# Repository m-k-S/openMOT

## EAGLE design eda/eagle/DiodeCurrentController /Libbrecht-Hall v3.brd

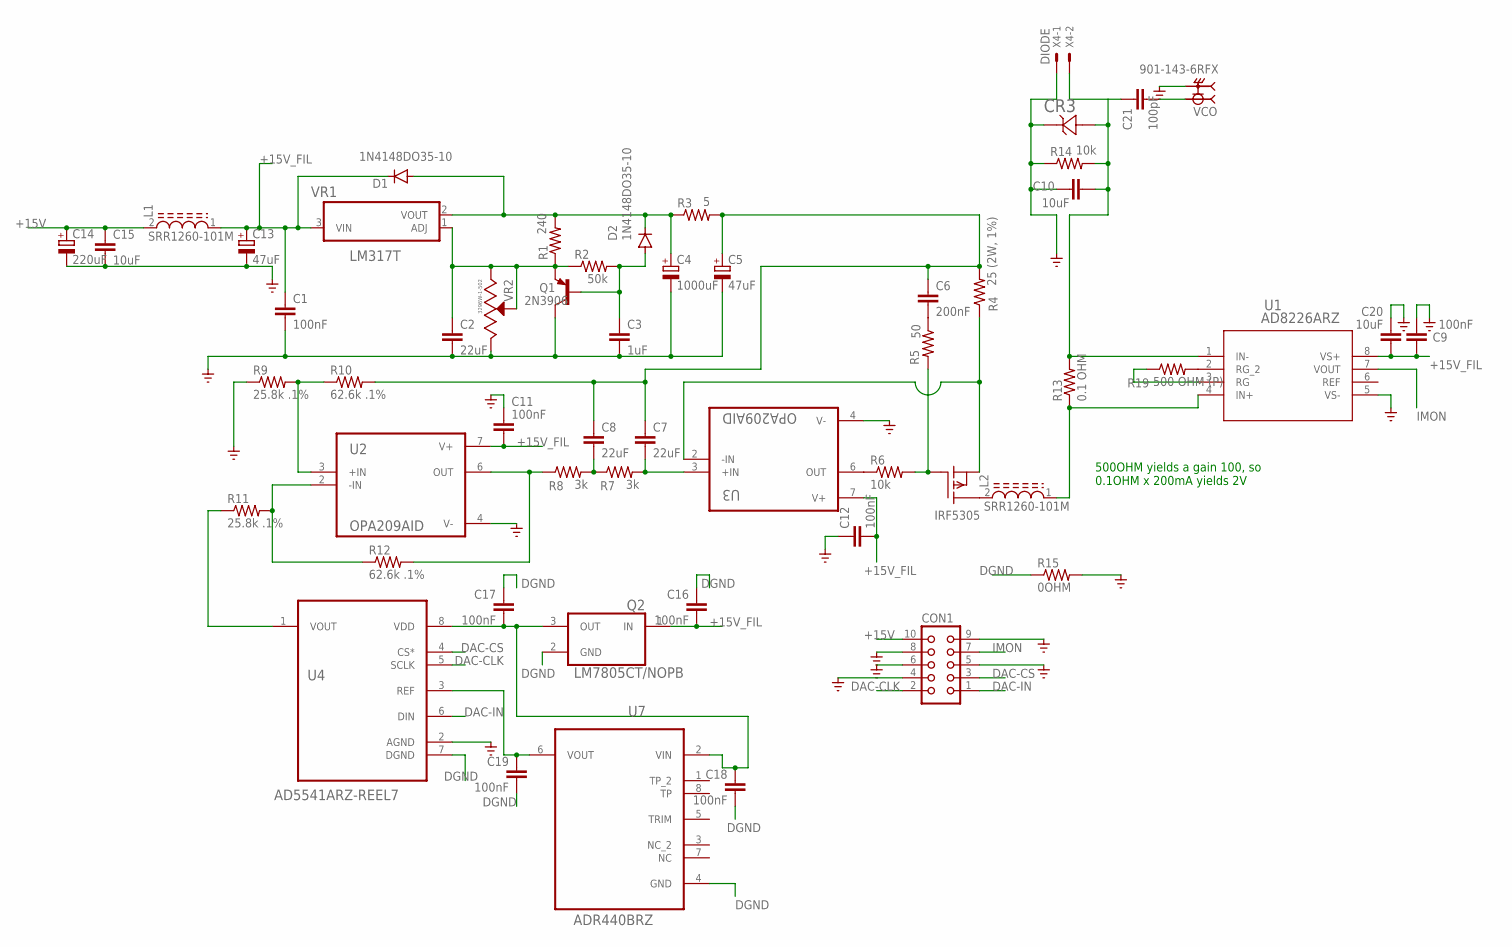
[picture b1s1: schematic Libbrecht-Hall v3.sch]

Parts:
C1, C11, C12, C16, C17, C18, C19: 100nF; C1206
C2, C7, C8: 22uF; C1206
C3: 1uF; C1206
C4: 1000uF; E5-13
C5, C13: 47uF; 175TMP-0808
C6: 200nF; C1206
C9: 100nF; C0603
C10, C15: 10uF; C1206
C14: 220uF; E3,5-8
C20: 10uF; C0603
C21: 100pF; C0603
CON1: CON10
CR3: ESDA7P60-1U1MZDO_1610_STM-M; ZDO_1610_STM-M
D1, D2: 1N4148DO35-10; DO35-10
IRF5305: IRF9530; TO220
L1, L2: SRR1260-101M; INDP125125X600N
Q1: 2N3906; TO92
Q2: LM7805CT/NOPB; TO254P1054X470X2600-3
R1: 240; R1206
R2: 50k; R1206
R3: 5; R1206
R4: 25 (2W, 1%); R1206
R5: 50; R1206
R6, R14: 10k; R1206
R7, R8: 3k; R1206
R9, R11: 25.8k .1%; R0603
R10, R12: 62.6k .1%; R0603
R13: 0.1 OHM; R1206
R15: 0OHM; R1206
R19: 500 OHM (P); R1206
U1: AD8226ARZ; R_8_ADI
U2, U3: OPA209AID; SOIC127P599X175-8N
U4: AD5541ARZ-REEL7; SOIC127P600X175-8N
U7: ADR440BRZ; SOIC127P600X175-8N
VCO: 901-143-6RFX; AMPHENOL_901-143-6RFX
VR1: LM317T; TO254P1054X470X1955-3
VR2: 3296W-1-502; TRIM_3296W-1-502
X4: DIODE; JST-XH-02-PACKAGE-LONG-PAD

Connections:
+15V: C14.+, C15.1, CON1.10, L1.2
+15V_FIL: C1.1, C9.2, C11.2, C12.2, C13.+, C16.2, C20.2, D1.C, L1.1, Q2.1 (IN), U1.8 (VS+), U2.7 (V+), U3.7 (V+), VR1.3 (VIN)
DAC-CLK: CON1.2, U4.5 (SCLK)
DAC-CS: CON1.3, U4.4 (CS*)
DAC-IN: CON1.1, U4.6 (DIN)
DGND: C16.1, C17.1, C18.2, C19.2, Q2.2 (GND), R15.1, U4.7 (DGND), U7.4 (GND)
GND: C1.2, C2.2, C3.2, C4.-, C5.-, C9.1, C10.1, C11.1, C12.1, C13.-, C14.-, C15.2, C20.1, CON1.4, CON1.5, CON1.6, CON1.8, CON1.9, CR3.1 (11), Q1.1 (C), R9.1, R14.1, R15.2, U1.5 (VS-), U2.4 (V-), U3.4 (V-), U4.2 (AGND), VCO.S1 (2), VCO.S2 (2), VCO.S3 (2), VCO.S4 (2), VR2.3 (CW), X4.1
IMON: CON1.7, U1.7 (VOUT)
unnamed: R11.1, U4.1 (VOUT)
unnamed: L2.1, R13.1, U1.4 (IN+)
unnamed: C5.+, C6.1, C7.1, C8.1, R3.2, R4.2, R10.2
unnamed: C4.+, D1.A, D2.C, R1.2, R3.1, VR1.2 (VOUT)
unnamed: C2.1, Q1.3 (E), R1.1, R2.1, VR1.1 (ADJ), VR2.1 (CCW), VR2.2 (WIPER)
unnamed: C10.2, C21.1, CR3.2 (12), R13.2, R14.2, U1.1 (IN-), X4.2
unnamed: C3.1, D2.A, Q1.2 (B), R2.2
unnamed: R6.1, U3.6 (OUT)
unnamed: R9.2, R10.1, U2.3 (+IN)
unnamed: C21.2, VCO.1
unnamed: C6.2, R5.1
unnamed: R19.2, U1.2 (RG_2)
unnamed: C19.1, U4.3 (REF), U7.6 (VOUT)
unnamed: C17.2, C18.1, Q2.3 (OUT), U4.8 (VDD), U7.2 (VIN)
unnamed: IRF5305.2 (D), L2.2
unnamed: R19.1, U1.3 (RG)
unnamed: IRF5305.3 (S), R4.1, U3.2 (-IN)
unnamed: C8.2, R7.1, R8.2
unnamed: C7.2, R7.2, U3.3 (+IN)
unnamed: R11.2, R12.1, U2.2 (-IN)
unnamed: R8.1, R12.2, U2.6 (OUT)
unnamed: IRF5305.1 (G), R5.2, R6.2

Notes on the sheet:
500OHM yields a gain 100, so 0.1OHM x 200mA yields 2V

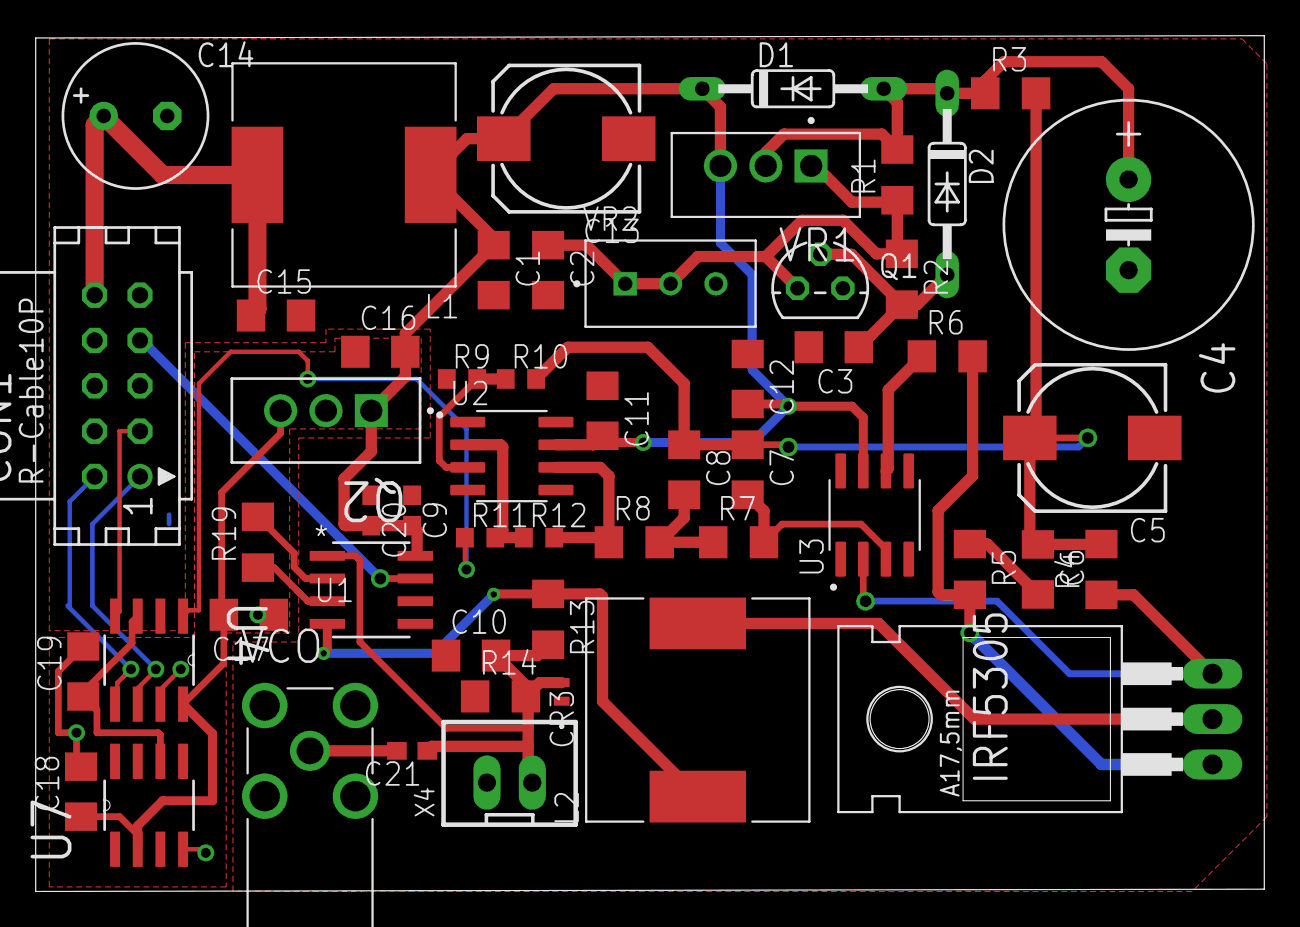
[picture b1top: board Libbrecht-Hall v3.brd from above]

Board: 2 copper layers, 68.8 x 47.9 mm, 55 parts (1 on the bottom side), 30 nets.

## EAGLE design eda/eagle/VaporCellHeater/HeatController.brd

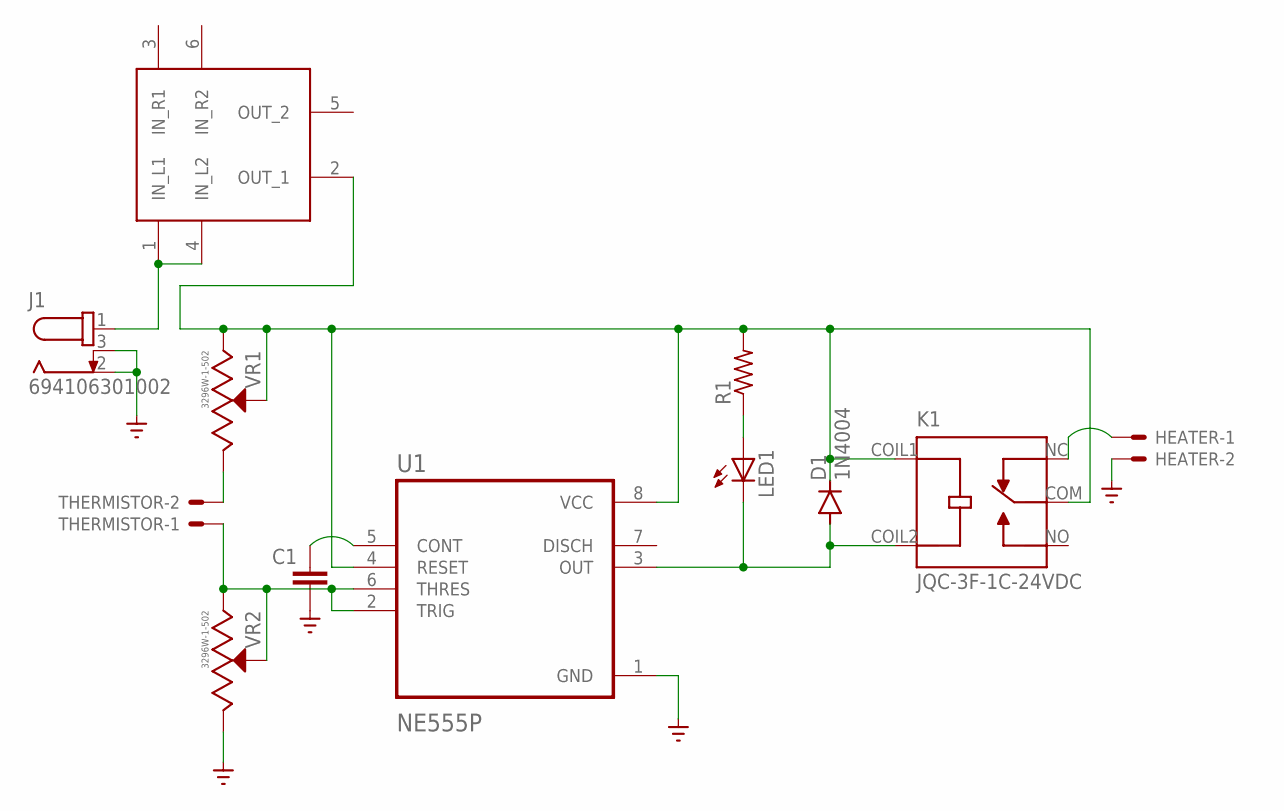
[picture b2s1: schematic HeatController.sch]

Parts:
C1: C-EUC0603; C0603
D1: 1N4004; DO41-10
HEATER: JST-XH-02-PIN-LONG-PAD; JST-XH-02-PACKAGE-LONG-PAD
J1: 694106301002
K1: JQC-3F-1C-24VDC; RELAY_JQC-3F-1C-24VDC
LED1: LED5MM
R1: R-US_0204/7; 0204/7
THERMISTOR: JST-XH-02-PIN-LONG-PAD; JST-XH-02-PACKAGE-LONG-PAD
U1: NE555P; DIP794W45P254L959H508Q8
U$1: 54-307PC
VR1, VR2: 3296W-1-502; TRIM_3296W-1-502

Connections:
GND: C1.1, HEATER.2, J1.2, J1.3, U1.1 (GND), VR2.3 (CW)
unnamed: THERMISTOR.1, U1.2 (TRIG), U1.6 (THRES), VR2.1 (CCW), VR2.2 (WIPER)
unnamed: J1.1, U$1.1 (IN_L1), U$1.4 (IN_L2)
unnamed: HEATER.1, K1.NC
unnamed: C1.2, U1.5 (CONT)
unnamed: D1.C, K1.COIL1, K1.COM, R1.2, U1.4 (RESET), U1.8 (VCC), U$1.2 (OUT_1), VR1.1 (CCW), VR1.2 (WIPER)
unnamed: THERMISTOR.2, VR1.3 (CW)
unnamed: D1.A, K1.COIL2, LED1.K (C), U1.3 (OUT)
unnamed: LED1.A, R1.1

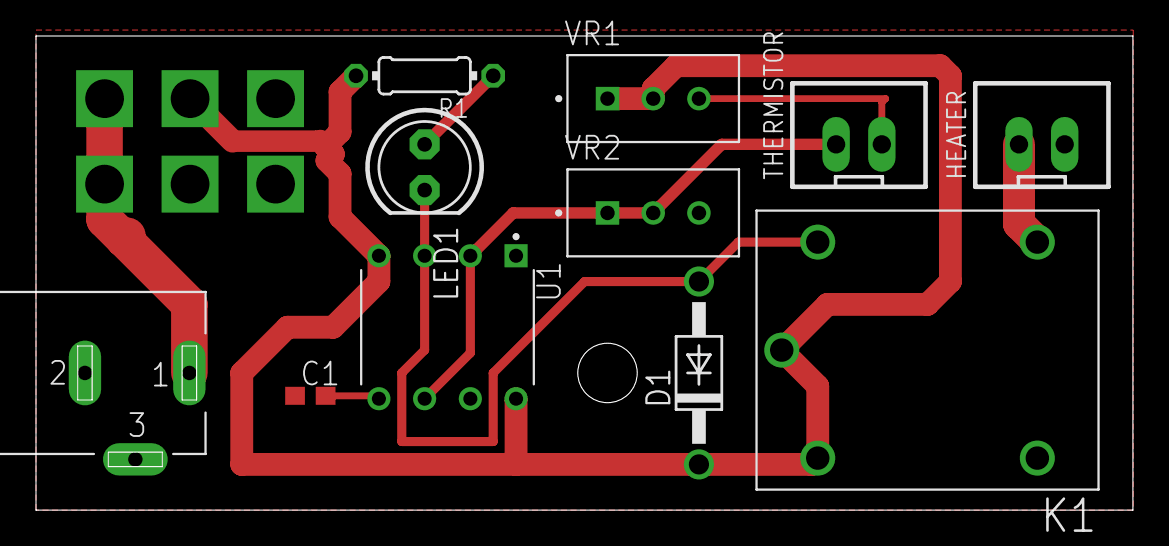
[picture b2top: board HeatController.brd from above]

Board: 2 copper layers, 60.9 x 26.3 mm, 12 parts (0 on the bottom side), 9 nets.

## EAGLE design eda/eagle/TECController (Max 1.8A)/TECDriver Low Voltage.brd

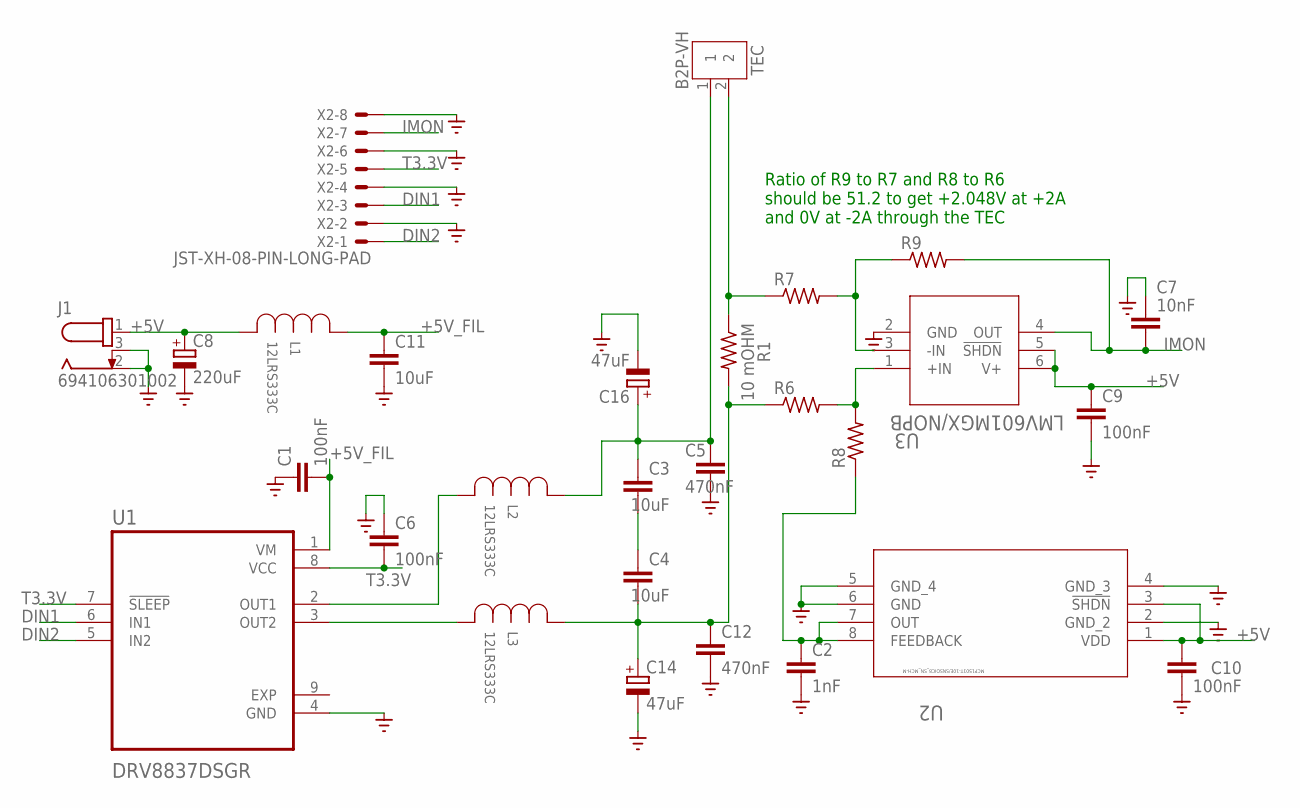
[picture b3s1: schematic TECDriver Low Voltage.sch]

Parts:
C1, C6, C9, C10: 100nF; C0603
C2: 1nF; C0603
C3, C4, C11: 10uF; C1206
C5, C12: 470nF; C1206
C7: 10nF; C0603
C8: 220uF; E3,5-8
C14, C16: 47uF; 175TMP-0808
J1: 694106301002
L1, L2, L3: 12LRS333C; IND_MURATA_1200LRS_MUR
R1: 10 mOHM; R1206
R6, R7, R8, R9: R-US_R1206; R1206
TEC: B2P-VH; B2P-VH_396-2N
U1: DRV8837DSGR; SON50P200X200X80-9N
U2: MCP1501T-10E/SNSOIC8_SN_MCH-M; SOIC8_SN_MCH-M
U3: LMV601MGX/NOPB; DCK6_TEX
X2: JST-XH-08-PIN-LONG-PAD; JST-XH-08-PACKAGE-LONG-PAD

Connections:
+5V: C8.+, C9.1, C10.1, J1.1, L1.3, U2.1 (VDD), U2.3 (!SHDN), U3.5 (!SHDN), U3.6 (V+)
+5V_FIL: C1.2, C11.1, L1.1, U1.1 (VM)
DIN1: U1.6 (IN1), X2.3
DIN2: U1.5 (IN2), X2.1
EXP: U1.9 (EXP)
GND: C1.1, C2.2, C5.2, C6.1, C7.1, C8.-, C9.2, C10.2, C11.2, C12.2, C14.-, C16.-, J1.2, J1.3, U1.4 (GND), U2.2 (GND_2), U2.4 (GND_3), U2.5 (GND_4), U2.6 (GND), U3.2 (GND), X2.2, X2.4, X2.6, X2.8
IMON: C7.2, R9.2, U3.4 (OUT), X2.7
unnamed: R6.2, R8.2, U3.1 (+IN)
unnamed: C2.1, R8.1, U2.7 (OUT), U2.8 (FEEDBACK)
unnamed: L2.3, U1.2 (OUT1)
unnamed: L3.3, U1.3 (OUT2)
unnamed: R7.2, R9.1, U3.3 (-IN)
unnamed: C3.1, C5.1, C16.+, L2.1, TEC.1
unnamed: C3.2, C4.1
unnamed: C4.2, C12.1, C14.+, L3.1, R1.2, R6.1
unnamed: R1.1, R7.1, TEC.2
T3.3V: C6.2, U1.7 (!SLEEP), U1.8 (VCC), X2.5

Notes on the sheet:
Ratio of R9 to R7 and R8 to R6 should be 51.2 to get +2.048V at +2A and 0V at -2A through the TEC

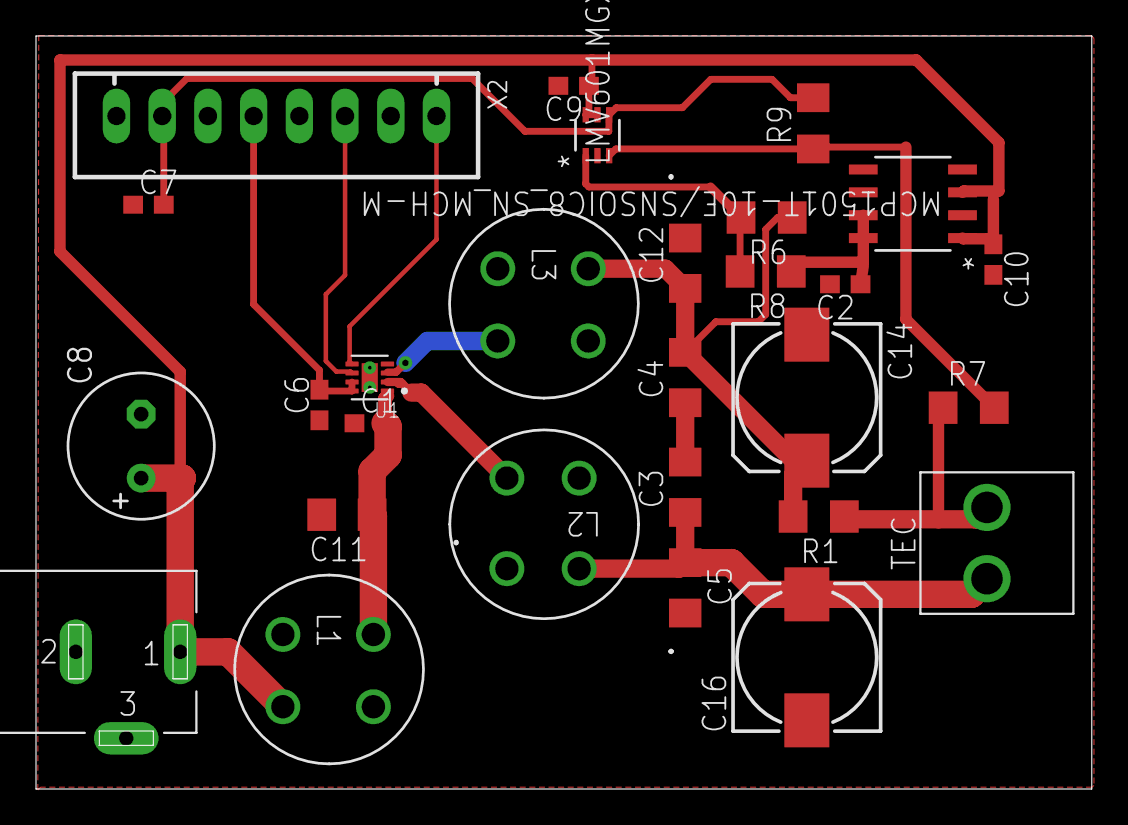
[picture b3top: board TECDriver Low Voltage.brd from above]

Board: 2 copper layers, 58.6 x 41.8 mm, 28 parts (0 on the bottom side), 16 nets.

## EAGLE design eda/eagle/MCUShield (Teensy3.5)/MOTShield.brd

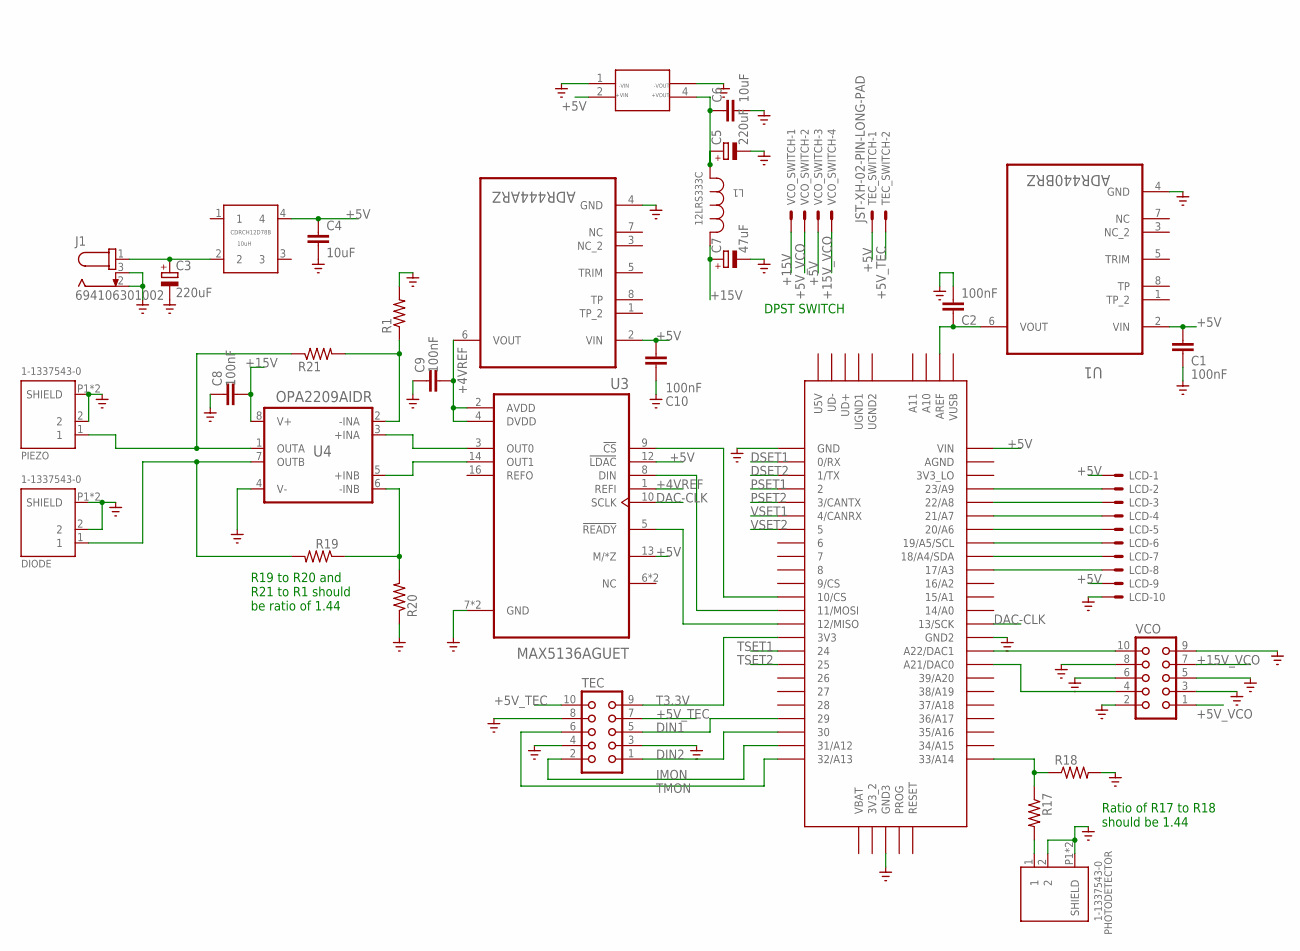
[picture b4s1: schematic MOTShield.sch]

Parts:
ADR444ARZ: ADR440BRZ; SOIC127P600X175-8N
C1, C2, C8, C9, C10: 100nF; C0603
C3, C5: 220uF; E3,5-8
C4, C6: 10uF; C1206
C7: 47uF; 175TMP-0808
DIODE: 1-1337543-0; CONN_1-1337543-0
J1: 694106301002
L1: 12LRS333C; IND_MURATA_1200LRS_MUR
LCD: JST-XH-10-PIN-LONG-PAD; JST-XH-10-PACKAGE-LONG-PAD
PHOTODETECTOR: 1-1337543-0; CONN_1-1337543-0
PIEZO: 1-1337543-0; CONN_1-1337543-0
R1, R17, R18, R19, R20, R21: R-US_R1206; R1206
TEC: CON10
TEC_SWITCH: JST-XH-02-PIN-LONG-PAD; JST-XH-02-PACKAGE-LONG-PAD
U1: ADR440BRZ; SOIC127P600X175-8N
U3: MAX5136AGUET; SOP65P640X110-16N
U4: OPA2209AIDR; SOIC127P599X175-8N
U$1: TEENSY_3.5/3.6
U$2: CRE1S0515SC; SIP625W50P254L1173H771Q4
U$3: 10uH; INDDFN1220X1220X800-4N
VCO: CON10
VCO_SWITCH: JST-XH-04-PIN-LONG-PAD; JST-XH-04-PACKAGE-LONG-PAD

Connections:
+4VREF: ADR444ARZ.6 (VOUT), C9.2, U3.1 (REFI), U3.2 (AVDD), U3.4 (DVDD)
+5V: ADR444ARZ.2 (VIN), C1.2, C4.1, C10.2, LCD.1, LCD.9, TEC_SWITCH.1, U1.2 (VIN), U3.12 (!LDAC), U3.13 (M/*Z), U$1.VIN, U$2.2 (+VIN), U$3.4, VCO_SWITCH.3
+5V_TEC: TEC.7, TEC.10, TEC_SWITCH.2
+5V_VCO: VCO.1, VCO_SWITCH.2
+15V: C7.+, C8.2, L1.1, U4.8 (V+), VCO_SWITCH.1
+15V_VCO: VCO.7, VCO_SWITCH.4
DAC-CLK: U3.10 (SCLK), U$1.13/SCK
DIN1: TEC.5, U$1.29
DIN2: TEC.1, U$1.30
DSET1: U$1.0/RX
DSET2: U$1.1/TX
GND: ADR444ARZ.4 (GND), C1.1, C2.2, C3.-, C4.2, C5.-, C6.2, C7.-, C8.1, C9.1, C10.1, DIODE.2, DIODE.P1 (SHIELD), DIODE.P2 (SHIELD), J1.2, J1.3, LCD.10, PHOTODETECTOR.2, PHOTODETECTOR.P1 (SHIELD), PHOTODETECTOR.P2 (SHIELD), PIEZO.2, PIEZO.P1 (SHIELD), PIEZO.P2 (SHIELD), R1.2, R18.2, R20.1, TEC.3, TEC.4, TEC.8, U1.4 (GND), U3.7 (GND), U3.15 (GND), U4.4 (V-), U$1.GND, U$1.GND2, U$1.GND3, U$2.1 (-VIN), U$2.3 (-VOUT), VCO.2, VCO.3, VCO.5, VCO.6, VCO.8, VCO.9
IMON: TEC.2, U$1.31/A12
unnamed: U3.3 (OUT0), U4.3 (+INA)
unnamed: PHOTODETECTOR.1, R17.2
unnamed: U$1.21/DAC0 (A21/DAC0), VCO.4
unnamed: C3.+, J1.1, U$3.2
unnamed: LCD.2, U$1.23/A9
unnamed: LCD.3, U$1.22/A8
unnamed: LCD.4, U$1.21/A7
unnamed: C5.+, C6.1, L1.3, U$2.4 (+VOUT)
unnamed: LCD.5, U$1.20/A6
unnamed: LCD.6, U$1.19/A5/SCL
unnamed: LCD.7, U$1.18/A4/SDA
unnamed: LCD.8, U$1.17/A3
unnamed: U$1.A22/DAC1, VCO.10
unnamed: R17.1, R18.1, U$1.33/A14
unnamed: U3.5 (!READY), U$1.12/MISO
unnamed: U3.8 (DIN), U$1.11/MOSI
unnamed: U3.9 (!CS), U$1.10/CS
unnamed: C2.1, U1.6 (VOUT), U$1.AREF
unnamed: U3.14 (OUT1), U4.5 (+INB)
unnamed: R19.1, R20.2, U4.6 (-INB)
unnamed: PIEZO.1, R21.1, U4.1 (OUTA)
unnamed: R1.1, R21.2, U4.2 (-INA)
unnamed: DIODE.1, R19.2, U4.7 (OUTB)
PSET1: U$1.2
PSET2: U$1.3/CANTX
T3.3V: TEC.9, U$1.3V3
TMON: TEC.6, U$1.32/A13
TSET1: U$1.24
TSET2: U$1.25
VSET1: U$1.4/CANRX
VSET2: U$1.5

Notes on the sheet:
Ratio of R17 to R18 should be 1.44
DPST SWITCH
R19 to R20 and R21 to R1 should be ratio of 1.44

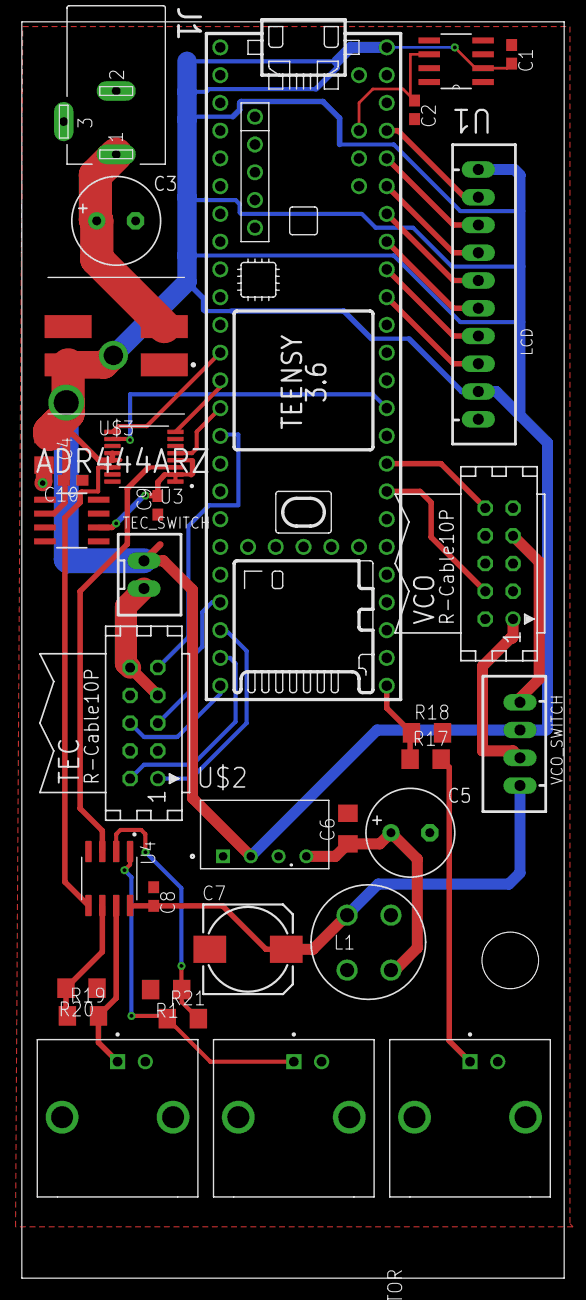
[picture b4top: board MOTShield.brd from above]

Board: 2 copper layers, 49.6 x 115.0 mm, 33 parts (0 on the bottom side), 36 nets.

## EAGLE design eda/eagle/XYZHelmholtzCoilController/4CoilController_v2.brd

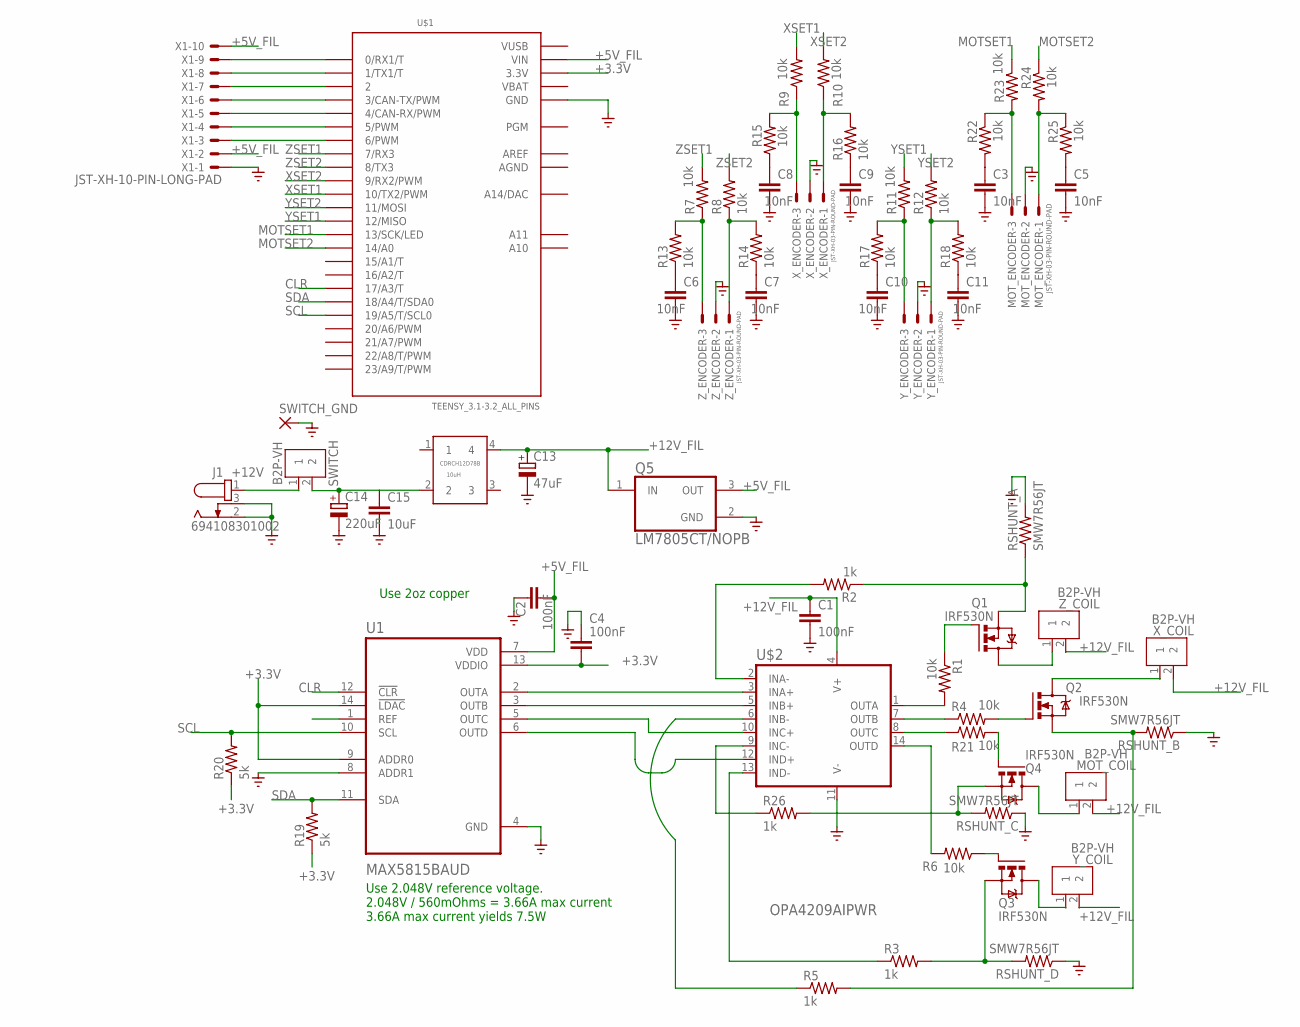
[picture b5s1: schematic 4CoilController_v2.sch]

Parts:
C1, C2, C4: 100nF; C0603
C3, C5, C6, C7, C8, C9, C10, C11: 10nF; C0603
C13: 47uF; 175TMP-0808
C14: 220uF; E3,5-8
C15: 10uF; C1206
J1: 694108301002
MOT_COIL: B2P-VH; B2P-VH_396-2N
MOT_ENCODER: JST-XH-03-PIN-ROUND-PAD; JST-XH-03-PACKAGE-ROUND-PAD
Q1, Q2, Q3, Q4: IRF530N; TO220BV
Q5: LM7805CT/NOPB; TO254P1054X470X2600-3
R1, R4, R6: 10k; R1206
R2, R3, R5: 1k; R1206
R7, R8, R9, R10, R11, R12, R13, R14, R15, R16, R17, R18, R21, R22, R23, R24, R25: 10k; R0603
R19, R20: 5k; R0603
R26: 1k; R0603
RSHUNT_A: SMW7R56JT
RSHUNT_B: SMW7R56JT
RSHUNT_C: SMW7R56JT
RSHUNT_D: SMW7R56JT
SWITCH: B2P-VH; B2P-VH_396-2N
SWITCH_GND: 3,81/1,4
U1: MAX5815BAUD; SOP65P640X110-14N
U$1: TEENSY_3.1-3.2_ALL_PINS; TEENSY_3.0-3.2&LC_ALL_PINS
U$2: OPA4209AIPWR; SOP65P640X120-14N
U$3: 10uH; INDDFN1220X1220X800-4N
X1: JST-XH-10-PIN-LONG-PAD; JST-XH-10-PACKAGE-LONG-PAD
X_COIL: B2P-VH; B2P-VH_396-2N
X_ENCODER: JST-XH-03-PIN-ROUND-PAD; JST-XH-03-PACKAGE-ROUND-PAD
Y_COIL: B2P-VH; B2P-VH_396-2N
Y_ENCODER: JST-XH-03-PIN-ROUND-PAD; JST-XH-03-PACKAGE-ROUND-PAD
Z_COIL: B2P-VH; B2P-VH_396-2N
Z_ENCODER: JST-XH-03-PIN-ROUND-PAD; JST-XH-03-PACKAGE-ROUND-PAD

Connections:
+3.3V: C4.2, R19.1, R20.1, U1.9 (ADDR0), U1.13 (VDDIO), U1.14 (!LDAC), U$1.3.3V, U$1.3.3V1 (3.3V)
+5V_FIL: C2.2, Q5.3 (OUT), U1.7 (VDD), U$1.VIN, X1.2, X1.10
+12V: C14.+, C15.1, SWITCH.2, U$3.2
+12V_FIL: C1.1, C13.+, MOT_COIL.2, Q5.1 (IN), U$2.4 (V+), U$3.4, X_COIL.2, Y_COIL.2, Z_COIL.2
AGND: U$1.AGND
AREF: U$1.AREF
CLR: U1.12 (!CLR), U$1.17/A3 (17/A3/T)
GND: C1.2, C2.1, C3.2, C4.1, C5.2, C6.2, C7.2, C8.2, C9.2, C10.2, C11.2, C13.-, C14.-, C15.2, J1.2, J1.3, MOT_ENCODER.2, Q5.2 (GND), RSHUNT_A.P$2 (2), RSHUNT_B.P$1 (1), RSHUNT_C.P$1 (1), RSHUNT_D.P$1 (1), SWITCH_GND.1, U1.4 (GND), U1.8 (ADDR1), U$1.GND, U$1.GND1 (GND), U$2.11 (V-), X1.1, X_ENCODER.2, Y_ENCODER.2, Z_ENCODER.2
MOTSET1: R23.1, U$1.13 (13/SCK/LED)
MOTSET2: R24.1, U$1.14/A0
unnamed: U1.6 (OUTD), U$2.12 (IND+)
unnamed: U1.3 (OUTB), U$2.5 (INB+)
unnamed: R5.1, U$2.6 (INB-)
unnamed: U1.2 (OUTA), U$2.3 (INA+)
unnamed: R1.2, U$2.1 (OUTA)
unnamed: R2.2, U$2.2 (INA-)
unnamed: Q1.G, R1.1
unnamed: Q1.S, R2.1, RSHUNT_A.P$1 (1)
unnamed: R7.1, R13.2, Z_ENCODER.3
unnamed: Q1.D, Z_COIL.1
unnamed: R8.1, R14.2, Z_ENCODER.1
unnamed: R4.1, U$2.7 (OUTB)
unnamed: Q2.G, R4.2
unnamed: Q2.S, R5.2, RSHUNT_B.P$2 (2)
unnamed: R3.1, U$2.13 (IND-)
unnamed: R6.2, U$2.14 (OUTD)
unnamed: Q2.D, X_COIL.1
unnamed: Q3.G, R6.1
unnamed: Q3.S, R3.2, RSHUNT_D.P$2 (2)
unnamed: Q3.D, Y_COIL.1
unnamed: R9.1, R15.2, X_ENCODER.3
unnamed: R10.1, R16.2, X_ENCODER.1
unnamed: R11.1, R17.2, Y_ENCODER.3
unnamed: R12.1, R18.2, Y_ENCODER.1
unnamed: C6.1, R13.1
unnamed: C7.1, R14.1
unnamed: C8.1, R15.1
unnamed: C9.1, R16.1
unnamed: C10.1, R17.1
unnamed: C11.1, R18.1
unnamed: J1.1, SWITCH.1
unnamed: U$1.0 (0/RX1/T), X1.9
unnamed: U$1.1 (1/TX1/T), X1.8
unnamed: U$1.2, X1.7
unnamed: U$1.3 (3/CAN-TX/PWM), X1.6
unnamed: U$1.4 (4/CAN-RX/PWM), X1.5
unnamed: U$1.5 (5/PWM), X1.4
unnamed: U$1.6 (6/PWM), X1.3
unnamed: U1.5 (OUTC), U$2.10 (INC+)
unnamed: R26.1, U$2.9 (INC-)
unnamed: R21.1, U$2.8 (OUTC)
unnamed: Q4.S, R26.2, RSHUNT_C.P$2 (2)
unnamed: Q4.G, R21.2
unnamed: MOT_COIL.1, Q4.D
unnamed: MOT_ENCODER.3, R22.1, R23.2
unnamed: MOT_ENCODER.1, R24.2, R25.1
unnamed: C3.1, R22.2
unnamed: C5.1, R25.2
SCL: R20.2, U1.10 (SCL), U$1.19/A5 (19/A5/T/SCL0)
SDA: R19.2, U1.11 (SDA), U$1.18/A4 (18/A4/T/SDA0)
VBAT: U$1.VBAT
VUSB: U$1.VUSB
XSET1: R9.2, U$1.10 (10/TX2/PWM)
XSET2: R10.2, U$1.9 (9/RX2/PWM)
YSET1: R11.2, U$1.12 (12/MISO)
YSET2: R12.2, U$1.11 (11/MOSI)
ZSET1: R7.2, U$1.7 (7/RX3)
ZSET2: R8.2, U$1.8 (8/TX3)

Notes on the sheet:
Use 2.048V reference voltage. 2.048V / 560mOhms = 3.66A max current 3.66A max current yields 7.5W
Use 2oz copper

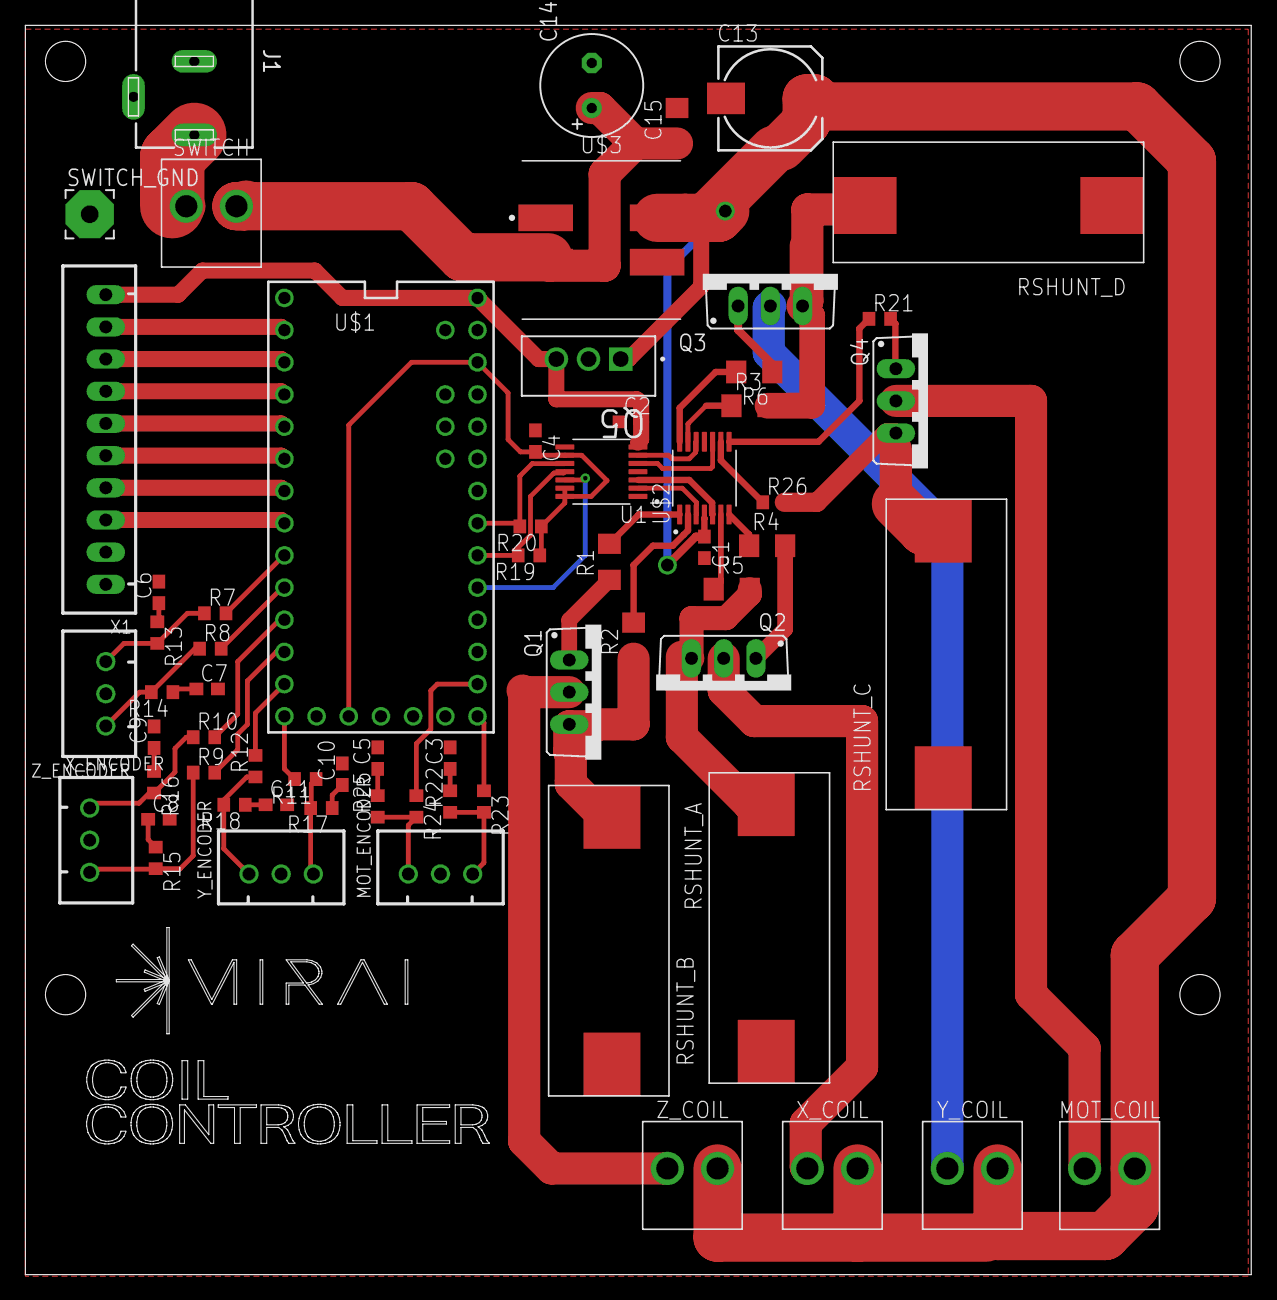
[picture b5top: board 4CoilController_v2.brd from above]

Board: 2 copper layers, 96.8 x 98.6 mm, 65 parts (0 on the bottom side), 64 nets.

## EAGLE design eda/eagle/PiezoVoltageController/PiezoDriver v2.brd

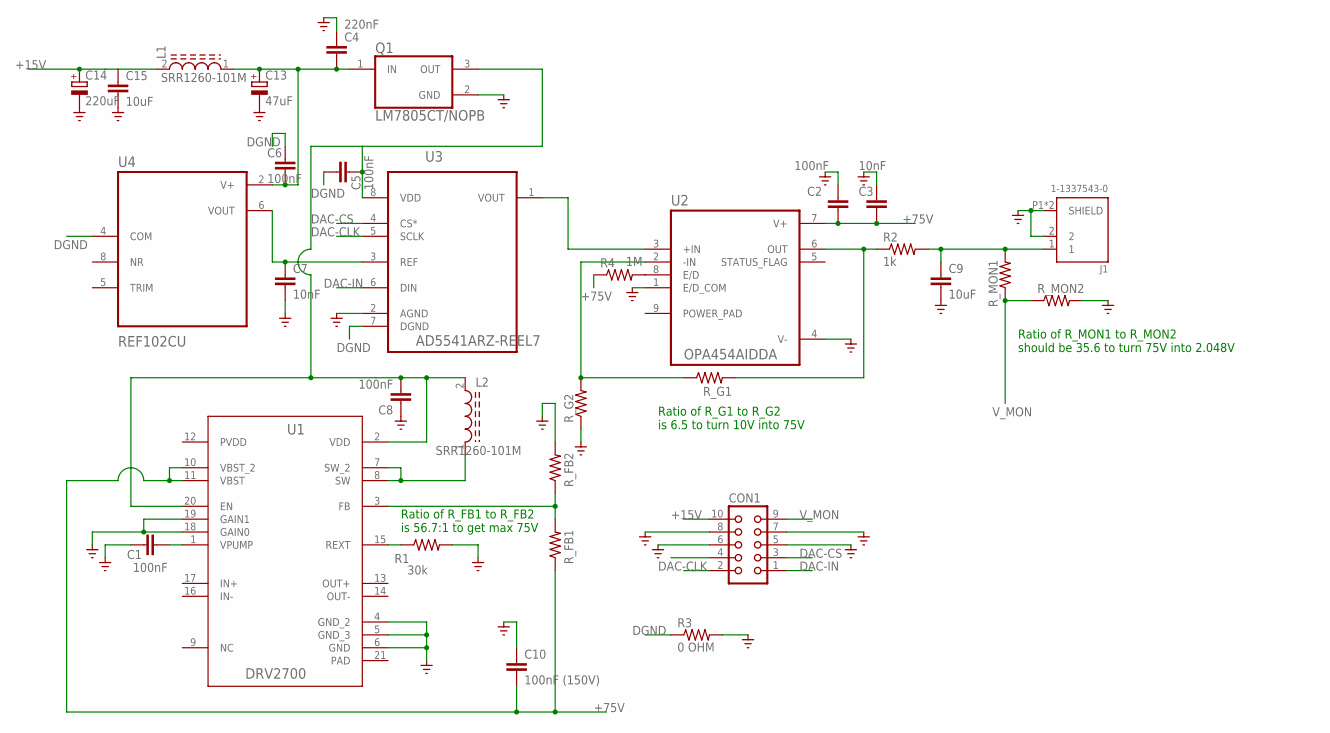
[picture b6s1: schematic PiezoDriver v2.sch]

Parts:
C1, C2, C5, C6, C8: 100nF; C1206
C3, C7: 10nF; C1206
C4: 220nF; C1206
C9, C15: 10uF; C1206
C10: 100nF (150V); C1206
C13: 47uF; 175TMP-0808
C14: 220uF; E3,5-8
CON1: CON10
J1: 1-1337543-0; CONN_1-1337543-0
L1, L2: SRR1260-101M; INDP125125X600N
Q1: LM7805CT/NOPB; TO254P1054X470X2600-3
R1: 30k; R1206
R2: 1k; R1206
R3: 0 OHM; R1206
R4: 1M; R1206
R_FB1, R_FB2: R-US_R1206; R1206
R_G1, R_G2: R-US_R1206; R1206
R_MON1, R_MON2: R-US_R1206; R1206
U1: DRV2700; RGP0020D
U2: OPA454AIDDA; VREG_LM5017MR/NOPB
U3: AD5541ARZ-REEL7; SOIC127P600X175-8N
U4: REF102CU; SOIC127P599X175-8N

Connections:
+15V: C14.+, C15.1, CON1.10, L1.2
+75V: C2.2, C3.2, C10.2, R4.1, R_FB1.1, U1.10 (VBST_2), U1.11 (VBST), U2.7 (V+)
DAC-CLK: CON1.2, U3.5 (SCLK)
DAC-CS: CON1.3, U3.4 (CS*)
DAC-IN: CON1.1, U3.6 (DIN)
DGND: C5.1, C6.1, R3.1, U3.7 (DGND), U4.4 (COM)
GND: C1.1, C2.1, C3.1, C4.1, C7.2, C8.1, C9.2, C10.1, C13.-, C14.-, C15.2, CON1.5, CON1.6, CON1.7, CON1.8, J1.2, J1.P1 (SHIELD), J1.P2 (SHIELD), Q1.2 (GND), R1.2, R3.2, R_FB2.2, R_G2.1, R_MON2.2, U1.4 (GND_2), U1.5 (GND_3), U1.6 (GND), U1.18 (GAIN0), U1.19 (GAIN1), U2.1 (E/D_COM), U2.4 (V-), U3.2 (AGND)
unnamed: U2.3 (+IN), U3.1 (VOUT)
unnamed: R_G1.1, R_G2.2, U2.2 (-IN)
unnamed: C1.2, U1.1 (VPUMP)
unnamed: C7.1, U3.3 (REF), U4.6 (VOUT)
unnamed: R1.1, U1.15 (REXT)
unnamed: C9.1, J1.1, R2.2, R_MON1.2
unnamed: L2.1, U1.7 (SW_2), U1.8 (SW)
unnamed: R4.2, U2.8 (E/D)
unnamed: R_FB1.2, R_FB2.1, U1.3 (FB)
unnamed: C5.2, C8.2, L2.2, Q1.3 (OUT), U1.2 (VDD), U1.20 (EN), U3.8 (VDD)
unnamed: R2.1, R_G1.2, U2.6 (OUT)
unnamed: C4.2, C6.2, C13.+, L1.1, Q1.1 (IN), U4.2 (V+)
PAD: U1.21 (PAD)
PVDD: U1.12 (PVDD)
V_MON: CON1.9, R_MON1.1, R_MON2.1

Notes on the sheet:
Ratio of R_FB1 to R_FB2 is 56.7:1 to get max 75V
Ratio of R_G1 to R_G2 is 6.5 to turn 10V into 75V
Ratio of R_MON1 to R_MON2 should be 35.6 to turn 75V into 2.048V

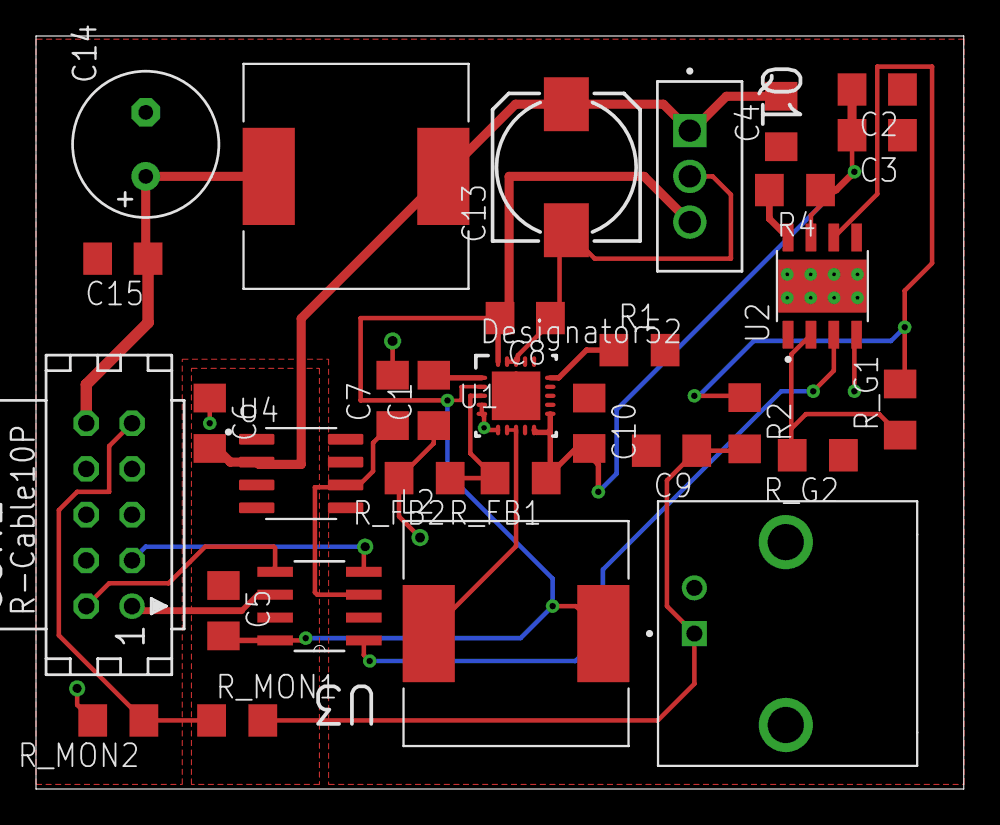
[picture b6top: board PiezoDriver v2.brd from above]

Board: 2 copper layers, 51.5 x 41.8 mm, 32 parts (1 on the bottom side), 20 nets.

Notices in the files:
parts and their libraries:
COPYRIGHT: Copyright (C) 2022 Ultra Librarian. All rights reserved.
COPYRIGHT: Copyright (C) 2018 Accelerated Designs. All rights reserved
COPYRIGHT: Copyright (C) 2021 Ultra Librarian. All rights reserved.
